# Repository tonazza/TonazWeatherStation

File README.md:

# TonazWeatherStation
Indoor weather station based on Raspberry Pi 2 model B

**2017/3/24**

Initial upload of the files.
Still NOT working, just a work in progress.

**PROJECT DESCRIPTION**

This is a Weather Station, conceived for measuring air properties in an indoor environment.

The main components are:

**Raspberry Pi 2 Model B** Single board computer

https://www.raspberrypi.org/products/raspberry-pi-2-model-b/

**MIDAS MC21605G12W-VNMLWI** LCD 16x2 chars I2C module, white on black

http://it.farnell.com/midas/mc21605g12w-vnmlwi/lcd-alpha-num-16-x-2-white/dp/2425704

**HONEYWELL HIH8131-000-001** humidity and temperature sensor

http://www.mouser.it/Search/ProductDetail.aspx?R=HIH8131-000-001virtualkey67850000virtualkey785-HIH8131-000-001

**MEASUREMENT SPECIALTIES MS580502BA01-50** barometric pressure sensor

http://www.mouser.it/Search/ProductDetail.aspx?R=MS580502BA01-50virtualkey53710000virtualkey824-MS580502BA01-50

The hardware project(Pi HAT + connection boards) was made using EAGLE CAD 6.5.

The software was made in Python 3, to be run on the Raspberry Pi equipped with Raspbian minimal on a 4GB uSD card.

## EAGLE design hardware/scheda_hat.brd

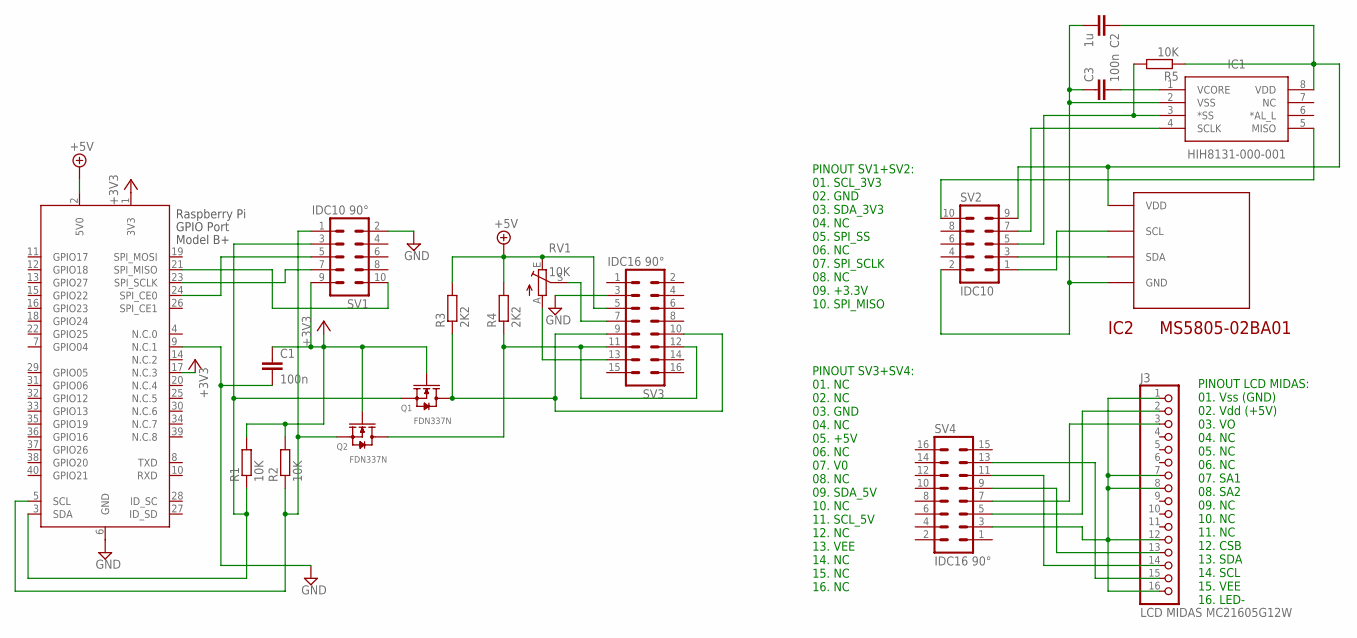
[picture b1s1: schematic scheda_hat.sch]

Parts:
C1, C3: 100n; C0805K
C2: 1u; C0805K
IC1: HIH8131-000-001; SOIC127P600X220-8N
IC2: MS5805-02BA01; MS5805-02BA
J3: LCD MIDAS MC21605G12W; 1X16
Q1, Q2: FDN337N; SOT95P230X110-3N
R1, R2, R5: 10K; R3216
R3, R4: 2K2; R3216
RV1: 10K; CA9V
SV1: IDC10 90°; ML10L
SV2: IDC10; ML10
SV3, SV4: IDC16 90°; ML16L
X1: RASPI_BOARD_B+_H; RASPI_BOARD_B+HAT

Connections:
+3V3: C1.1, Q1.1 (G1), Q2.1 (G1), R1.2, R2.2, SV1.9, X1.1 (3V3), X1.17 (N.C.3)
+5V: R3.2, R4.2, RV1.E, SV3.5, X1.2 (5V0)
GND: C1.2, SV1.2, SV3.3, X1.6 (GND), X1.9 (N.C.1)
unnamed: IC1.3 (*SS), R5.2, SV2.5
unnamed: J3.1, J3.7, J3.8, J3.12, J3.16, SV4.3
unnamed: RV1.A, SV3.13
unnamed: J3.15, SV4.13
unnamed: C2.2, C3.1, IC1.2 (VSS), IC2.P$4 (GND), SV2.2
unnamed: IC2.P$2 (SCL), SV2.1
unnamed: IC2.P$3 (SDA), SV2.3
unnamed: J3.2, SV4.5
unnamed: IC1.5 (MISO), SV2.10
unnamed: IC1.4 (SCLK), SV2.7
unnamed: J3.3, SV4.7
unnamed: J3.13, SV4.9
unnamed: J3.14, SV4.11
unnamed: C2.1, IC1.8 (VDD), IC2.P$1 (VDD), R5.1, SV2.9
SCL_3V3: Q2.2 (S1), R2.1, SV1.1, X1.5 (SCL)
SCL_5V: Q2.3 (D1), R4.1, SV3.11, SV3.12
SDA_3V3: Q1.2 (S1), R1.1, SV1.3, X1.3 (SDA)
SDA_5V: Q1.3 (D1), R3.1, SV3.9, SV3.10
SPI_MISO: SV1.10, X1.21 (SPI_MISO)
SPI_SCLK: SV1.7, X1.23 (SPI_SCLK)
SPI_SS: SV1.5, X1.24 (SPI_CE0)
V0: RV1.S, SV3.7
VCORE: C3.2, IC1.1 (VCORE)

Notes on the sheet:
PINOUT LCD MIDAS: 01. Vss (GND) 02. Vdd (+5V) 03. VO 04. NC 05. NC 06. NC 07. SA1 08. SA2 09. NC 10. NC 11. NC 12. CSB 13. SDA 14. SCL 15. VEE 16. LED-
PINOUT SV1+SV2: 01. SCL_3V3 02. GND 03. SDA_3V3 04. NC 05. SPI_SS 06. NC 07. SPI_SCLK 08. NC 09. +3.3V 10. SPI_MISO
PINOUT SV3+SV4: 01. NC 02. NC 03. GND 04. NC 05. +5V 06. NC 07. V0 08. NC 09. SDA_5V 10. NC 11. SCL_5V 12. NC 13. VEE 14. NC 15. NC 16. NC

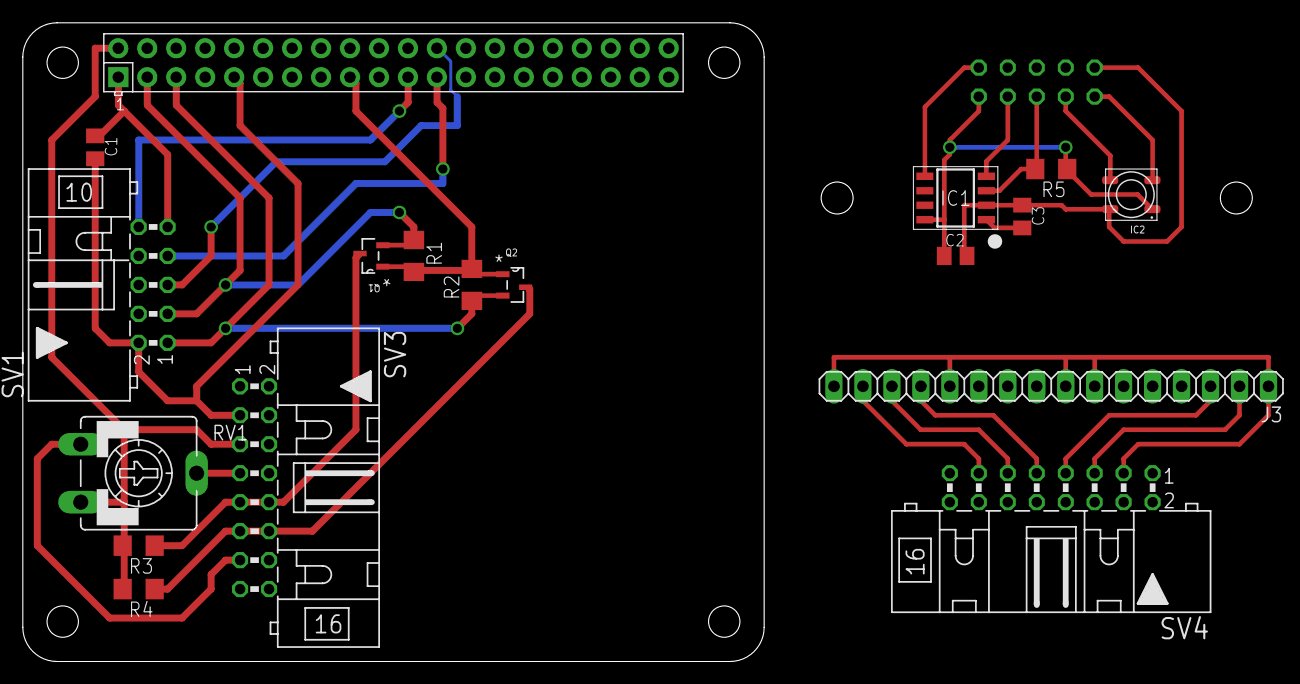
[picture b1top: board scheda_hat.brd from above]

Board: 2 copper layers, 65.0 x 56.0 mm, 19 parts (1 on the bottom side), 26 nets.

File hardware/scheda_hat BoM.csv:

"Part";"Value";"Device";"Package";"Description";"3D_PACKAGE";"DESCRIPTION";"HEIGHT";"MANUFACTURER_NAME";"MANUFACTURER_PART_NUMBER";"MF";"MPN";"OC_FARNELL";"OC_NEWARK";"PACKAGE";"RS_PART_NUMBER";"SUPPLIER";"SUPPLIER_NAME";
"C1";"100n";"C-EUC0805K";"C0805K";"CAPACITOR, European symbol";"";"";"";"";"";"";"";"";"";"";"";"";"";
"C2";"1u";"C-EUC0805K";"C0805K";"CAPACITOR, European symbol";"";"";"";"";"";"";"";"";"";"";"";"";"";
"C3";"100n";"C-EUC0805K";"C0805K";"CAPACITOR, European symbol";"";"";"";"";"";"";"";"";"";"";"";"";"";
"IC1";"HIH8131-000-001";"HIH8131-000-001";"SOIC127P600X220-8N";"Honeywell HIH8131-000-001 Humidity Sensor 8-Pin SOIC, -40  +125 C";"";"Honeywell HIH8131-000-001 Humidity Sensor 8-Pin SOIC, -40  +125 C";"2.2mm";"Honeywell";"HIH8131-000-001";"";"";"";"";"";"8748744";"";"RS";
"IC2";"MS5805-02BA01";"MS5805-02BA01";"MS5805-02BA";"Absolute Pressure Sensor";"";"";"";"";"";"";"";"";"";"";"";"";"";
"J3";"LCD MIDAS MC21605G12W";"PINHD-1X16";"1X16";"PIN HEADER";"";"";"";"";"";"";"";"";"";"";"";"";"";
"Q1";"FDN337N";"FDN337N";"SOT95P230X110-3N";"N-channel MOSFET";"";"";"";"";"";"";"FDN337N";"9845356";"";"SOT-23";"";"Fairchild";"";
"Q2";"FDN337N";"FDN337N";"SOT95P230X110-3N";"N-channel MOSFET";"";"";"";"";"";"";"FDN337N";"9845356";"";"SOT-23";"";"Fairchild";"";
"R1";"10K";"R-EU_R3216";"R3216";"RESISTOR, European symbol";"";"";"";"";"";"";"";"";"";"";"";"";"";
"R2";"10K";"R-EU_R3216";"R3216";"RESISTOR, European symbol";"";"";"";"";"";"";"";"";"";"";"";"";"";
"R3";"2K2";"R-EU_R3216";"R3216";"RESISTOR, European symbol";"";"";"";"";"";"";"";"";"";"";"";"";"";
"R4";"2K2";"R-EU_R3216";"R3216";"RESISTOR, European symbol";"";"";"";"";"";"";"";"";"";"";"";"";"";
"R5";"10K";"R-EU_R3216";"R3216";"RESISTOR, European symbol";"";"";"";"";"";"";"";"";"";"";"";"";"";
"RV1";"10K";"TRIM_EU-CA9V";"CA9V";"POTENTIOMETER";"";"";"";"";"";"";"";"";"";"";"";"";"";
"SV1";"IDC10 90°";"ML10L";"ML10L";"HARTING";"";"";"";"";"";"";"";"unknown";"unknown";"";"";"";"";
"SV2";"IDC10";"ML10";"ML10";"HARTING";"";"";"";"";"";"";"";"unknown";"unknown";"";"";"";"";
"SV3";"IDC16 90°";"ML16L";"ML16L";"HARTING";"";"";"";"";"";"";"";"unknown";"unknown";"";"";"";"";
"SV4";"IDC16 90°";"ML16L";"ML16L";"HARTING";"";"";"";"";"";"";"";"unknown";"unknown";"";"";"";"";
"X1";"RASPI_BOARD_B+_H";"RASPI_BOARD_B+_H";"RASPI_BOARD_B+HAT";"Raspberry Pi GPIO connector with markings for the outer dimensions of the Raspberry Pi board model B+";"";"";"";"";"";"";"";"";"";"";"";"";"";

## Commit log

2017-03-24 first commit of the README.
2017-03-24 correzione README.
2017-03-24 Added software and hardware files
